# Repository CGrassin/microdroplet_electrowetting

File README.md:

# µDroplet - Microfluidics platform

Microfluidics is an area of research based on the manipulation of small fluid volumes on the order of microliters or nanoliters.

µDroplet is an open-source platform with an 8&times;8 array of electrodes driven by a high voltage to expermiment with various microfluidics techniques and materials.

See article here: https://charleslabs.fr/en/project-Microfluidics+Electrowetting+platform

## Content

This repository contains:
* The PCB (including BOM and gerber files),
* The Arduino firmware
* The Processing control software
* The STL/CAD files for the 3D-printable base and frame

## License

The content of this repository is under MIT license.

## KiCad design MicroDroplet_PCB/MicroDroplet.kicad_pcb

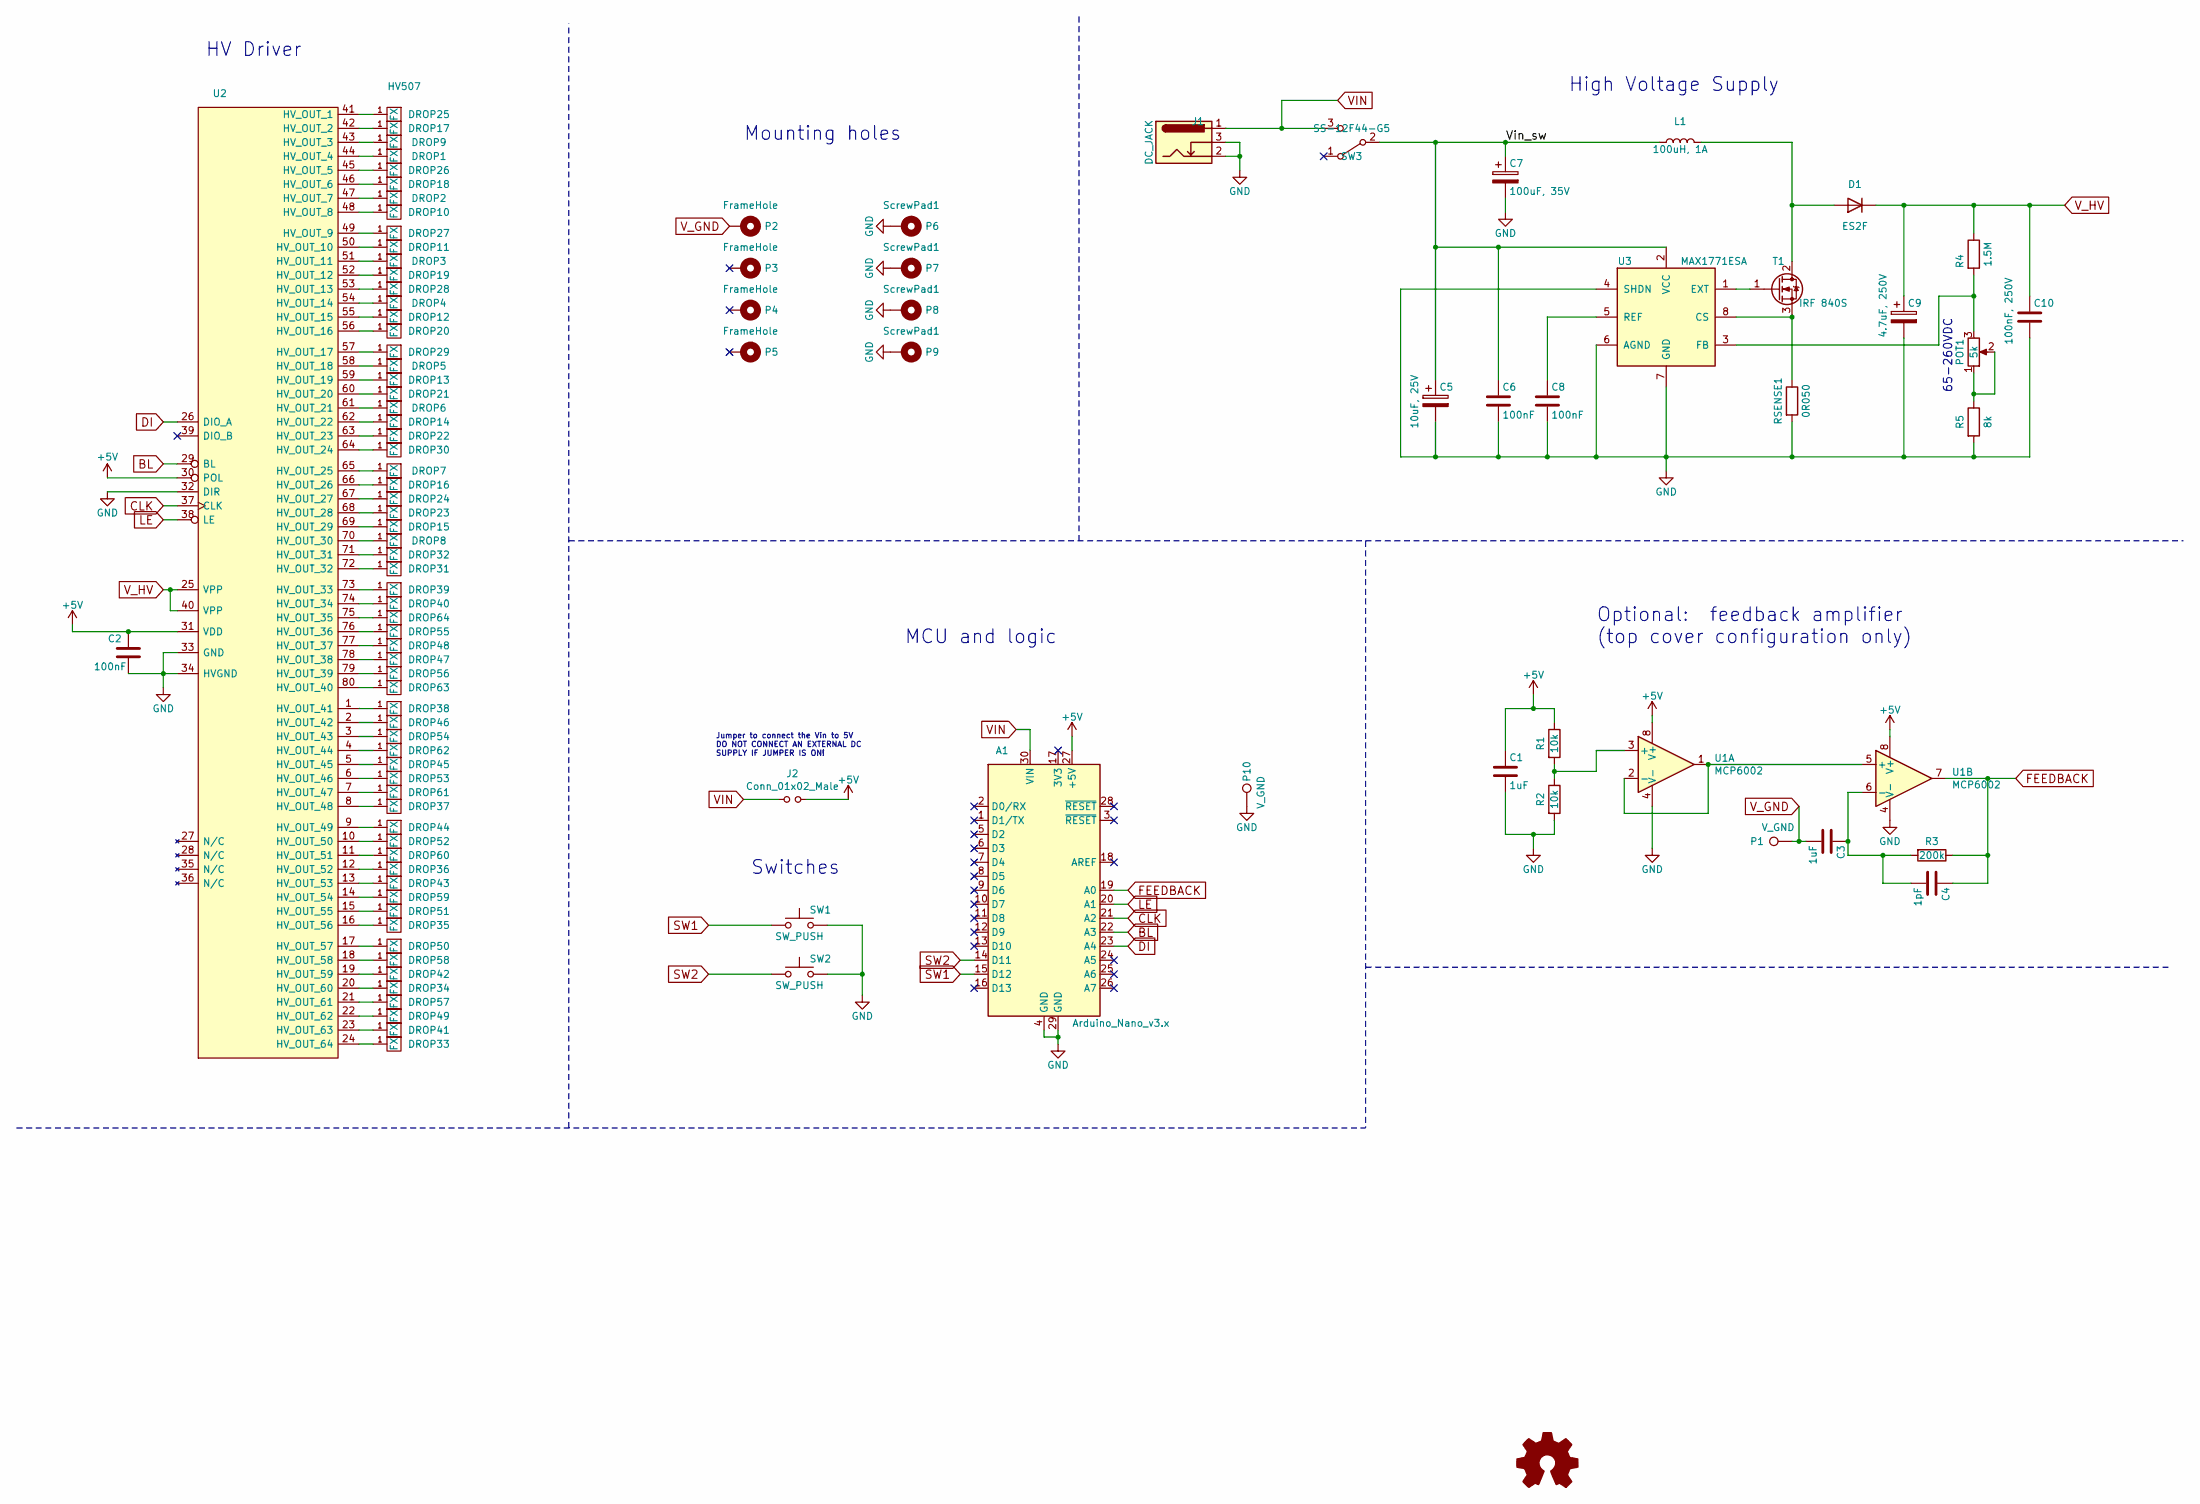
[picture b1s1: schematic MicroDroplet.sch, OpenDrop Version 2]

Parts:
A1: Arduino_Nano_v3.x; Arduino_Nano
C1, C3: 1uF; C_0805_2012Metric_Pad1.15x1.40mm_HandSolder; LCSC C28323
C2, C6, C8: 100nF; C_0805_2012Metric_Pad1.15x1.40mm_HandSolder; LCSC C476766
C4: 1pF; C_0805_2012Metric_Pad1.15x1.40mm_HandSolder; LCSC C1786
C5: 10uF, 25V; CP_Elec_5x5.4; LCSC C72487
C7: 100uF, 35V; CP_Elec_6.3x7.7; LCSC C99837
C9: 4.7uF, 250V; CP_Elec_10x10.5; LCSC C88703
C10: 100nF, 250V; C_1206_3216Metric_Pad1.42x1.75mm_HandSolder; LCSC C338139
D1: ES2F; D_SMB_Handsoldering; LCSC C145321
DROP1, DROP2, DROP3, DROP4, DROP5, DROP6, DROP7, DROP8, DROP9, DROP10, DROP11, DROP12, DROP13, DROP14, DROP15, DROP16, DROP17, DROP18, DROP19, DROP20, DROP21, DROP22, DROP23, DROP24, DROP25, DROP26, DROP27, DROP28, DROP29, DROP30, DROP31, DROP32, DROP33, DROP34, DROP35, DROP36, DROP37, DROP38, DROP39, DROP40, DROP41, DROP42, DROP43, DROP44, DROP45, DROP46, DROP47, DROP48, DROP49, DROP50, DROP51, DROP52, DROP53, DROP54, DROP55, DROP56, DROP57, DROP58, DROP59, DROP60, DROP61, DROP62, DROP63, DROP64: FX; DROP_2_75_4MIL_4_5
J1: DC_JACK; BarrelJack_Horizontal; LCSC C16214
J2: Conn_01x02_Male; PinHeader_1x02_P2.54mm_Vertical; LCSC C124375
L1: 100uH, 1A; L_Bourns_SRR1210A; LCSC C237992
LOGO1: Logo_Open_Hardware_Small; Charleslabs_Logo_10mm
P1, P10: V_GND; TestPoint_THTPad_D2.0mm_Drill1.0mm
P2: FrameHole; MountingHole_3.2mm_M3_Pad
P3, P4, P5: FrameHole; MountingHole_3.2mm_M3
P6, P7, P8, P9: ScrewPad1; MountingHole_3.2mm_M3_Pad
POT1: 5k; BOURNS-3362P_pot; LCSC C116296
R1, R2: 10k; R_0805_2012Metric_Pad1.15x1.40mm_HandSolder; LCSC C38522
R3: 200k; R_0805_2012Metric_Pad1.15x1.40mm_HandSolder; LCSC C104082
R4: 1.5M; R_1206_3216Metric_Pad1.42x1.75mm_HandSolder; LCSC C294796
R5: 8k; R_0805_2012Metric_Pad1.15x1.40mm_HandSolder; LCSC C465485
RSENSE1: 0R050; R_2512_6332Metric_Pad1.52x3.35mm_HandSolder; LCSC C160588
SW1, SW2: SW_PUSH; SW_PUSH_6mm; LCSC C393938
SW3: SS-12F44-G5; SPDT_12.1_5.6; LCSC C136718
T1: IRF 840S; TO-263-2; LCSC C134927
U1: MCP6002; SOIC-8_3.9x4.9mm_P1.27mm; LCSC C7377
U2: HV507; PQFP-80_14x20mm_P0.8mm
U3: MAX1771ESA; SOIC-8_3.9x4.9mm_P1.27mm

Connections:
+5V: A1.27 (+5V), C1.1, C2.1, J2.2, R1.1, U1.8 (V+), U2.30 (POL), U2.31 (VDD)
/Vin_sw: C5.1, C6.1, C7.1, L1.1, SW3.2 (B), U3.2 (VCC)
BL: A1.22 (A3), U2.29 (BL)
CLK: A1.21 (A2), U2.37 (CLK)
DI: A1.23 (A4), U2.26 (DIO_A)
FEEDBACK: A1.19 (A0), C4.1, R3.1, U1.7
GND: A1.4 (GND), A1.29 (GND), C1.2, C2.2, C5.2, C6.2, C7.2, C8.2, C9.2, C10.2, J1.2, J1.3, P6.1, P7.1, P8.1, P9.1, P10.1, R2.2, R5.2, RSENSE1.2, SW1.2, SW2.2, U1.4 (V-), U2.32 (DIR), U2.33 (GND), U2.34 (HVGND), U3.4 (SHDN), U3.6 (AGND), U3.7 (GND)
LE: A1.20 (A1), U2.38 (LE)
unnamed: C3.1, C4.2, R3.2, U1.6 (-)
unnamed: C8.1, U3.5 (REF)
unnamed: D1.2 (A), L1.2, T1.2 (D)
unnamed: DROP1.1, U2.44 (HV_OUT_4)
unnamed: DROP2.1, U2.47 (HV_OUT_7)
unnamed: DROP3.1, U2.51 (HV_OUT_11)
unnamed: DROP4.1, U2.54 (HV_OUT_14)
unnamed: DROP5.1, U2.58 (HV_OUT_18)
unnamed: DROP6.1, U2.61 (HV_OUT_21)
unnamed: DROP7.1, U2.65 (HV_OUT_25)
unnamed: DROP8.1, U2.70 (HV_OUT_30)
unnamed: DROP9.1, U2.43 (HV_OUT_3)
unnamed: DROP10.1, U2.48 (HV_OUT_8)
unnamed: DROP11.1, U2.50 (HV_OUT_10)
unnamed: DROP12.1, U2.55 (HV_OUT_15)
unnamed: DROP13.1, U2.59 (HV_OUT_19)
unnamed: DROP14.1, U2.62 (HV_OUT_22)
unnamed: DROP15.1, U2.69 (HV_OUT_29)
unnamed: DROP16.1, U2.66 (HV_OUT_26)
unnamed: DROP17.1, U2.42 (HV_OUT_2)
unnamed: DROP18.1, U2.46 (HV_OUT_6)
unnamed: DROP19.1, U2.52 (HV_OUT_12)
unnamed: DROP20.1, U2.56 (HV_OUT_16)
unnamed: DROP21.1, U2.60 (HV_OUT_20)
unnamed: DROP22.1, U2.63 (HV_OUT_23)
unnamed: DROP23.1, U2.68 (HV_OUT_28)
unnamed: DROP24.1, U2.67 (HV_OUT_27)
unnamed: DROP25.1, U2.41 (HV_OUT_1)
unnamed: DROP26.1, U2.45 (HV_OUT_5)
unnamed: DROP27.1, U2.49 (HV_OUT_9)
unnamed: DROP28.1, U2.53 (HV_OUT_13)
unnamed: DROP29.1, U2.57 (HV_OUT_17)
unnamed: DROP30.1, U2.64 (HV_OUT_24)
unnamed: DROP31.1, U2.72 (HV_OUT_32)
unnamed: DROP32.1, U2.71 (HV_OUT_31)
unnamed: DROP33.1, U2.24 (HV_OUT_64)
unnamed: DROP34.1, U2.20 (HV_OUT_60)
unnamed: DROP35.1, U2.16 (HV_OUT_56)
unnamed: DROP36.1, U2.12 (HV_OUT_52)
unnamed: DROP37.1, U2.8 (HV_OUT_48)
unnamed: DROP38.1, U2.1 (HV_OUT_41)
unnamed: DROP39.1, U2.73 (HV_OUT_33)
unnamed: DROP40.1, U2.74 (HV_OUT_34)
unnamed: DROP41.1, U2.23 (HV_OUT_63)
unnamed: DROP42.1, U2.19 (HV_OUT_59)
unnamed: DROP43.1, U2.13 (HV_OUT_53)
unnamed: DROP44.1, U2.9 (HV_OUT_49)
unnamed: DROP45.1, U2.5 (HV_OUT_45)
unnamed: DROP46.1, U2.2 (HV_OUT_42)
unnamed: DROP47.1, U2.78 (HV_OUT_38)
unnamed: DROP48.1, U2.77 (HV_OUT_37)
unnamed: DROP49.1, U2.22 (HV_OUT_62)
unnamed: DROP50.1, U2.17 (HV_OUT_57)
unnamed: DROP51.1, U2.15 (HV_OUT_55)
unnamed: DROP52.1, U2.10 (HV_OUT_50)
unnamed: DROP53.1, U2.6 (HV_OUT_46)
unnamed: DROP54.1, U2.3 (HV_OUT_43)
unnamed: DROP55.1, U2.76 (HV_OUT_36)
unnamed: DROP56.1, U2.79 (HV_OUT_39)
unnamed: DROP57.1, U2.21 (HV_OUT_61)
unnamed: DROP58.1, U2.18 (HV_OUT_58)
unnamed: DROP59.1, U2.14 (HV_OUT_54)
unnamed: DROP60.1, U2.11 (HV_OUT_51)
unnamed: DROP61.1, U2.7 (HV_OUT_47)
unnamed: DROP62.1, U2.4 (HV_OUT_44)
unnamed: DROP63.1, U2.80 (HV_OUT_40)
unnamed: DROP64.1, U2.75 (HV_OUT_35)
unnamed: POT1.1, POT1.2, R5.1
unnamed: POT1.3, R4.2, U3.3 (FB)
unnamed: R1.2, R2.1, U1.3 (+)
unnamed: RSENSE1.1, T1.3 (S), U3.8 (CS)
unnamed: T1.1 (G), U3.1 (EXT)
unnamed: U1.1, U1.2 (-), U1.5 (+)
SW1: A1.15 (D12), SW1.1
SW2: A1.14 (D11), SW2.1
VIN: A1.30 (VIN), J1.1, J2.1, SW3.3 (C)
V_GND: C3.2, P1.1, P2.1
V_HV: C9.1, C10.1, D1.1 (K), R4.1, U2.25 (VPP), U2.40 (VPP)

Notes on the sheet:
65-260VDC
High Voltage Supply
HV Driver
Switches
Jumper to connect the Vin to 5V DO NOT CONNECT AN EXTERNAL DC SUPPLY IF JUMPER IS ON!
Optional: feedback amplifier (top cover configuration only)
Mounting holes
MCU and logic

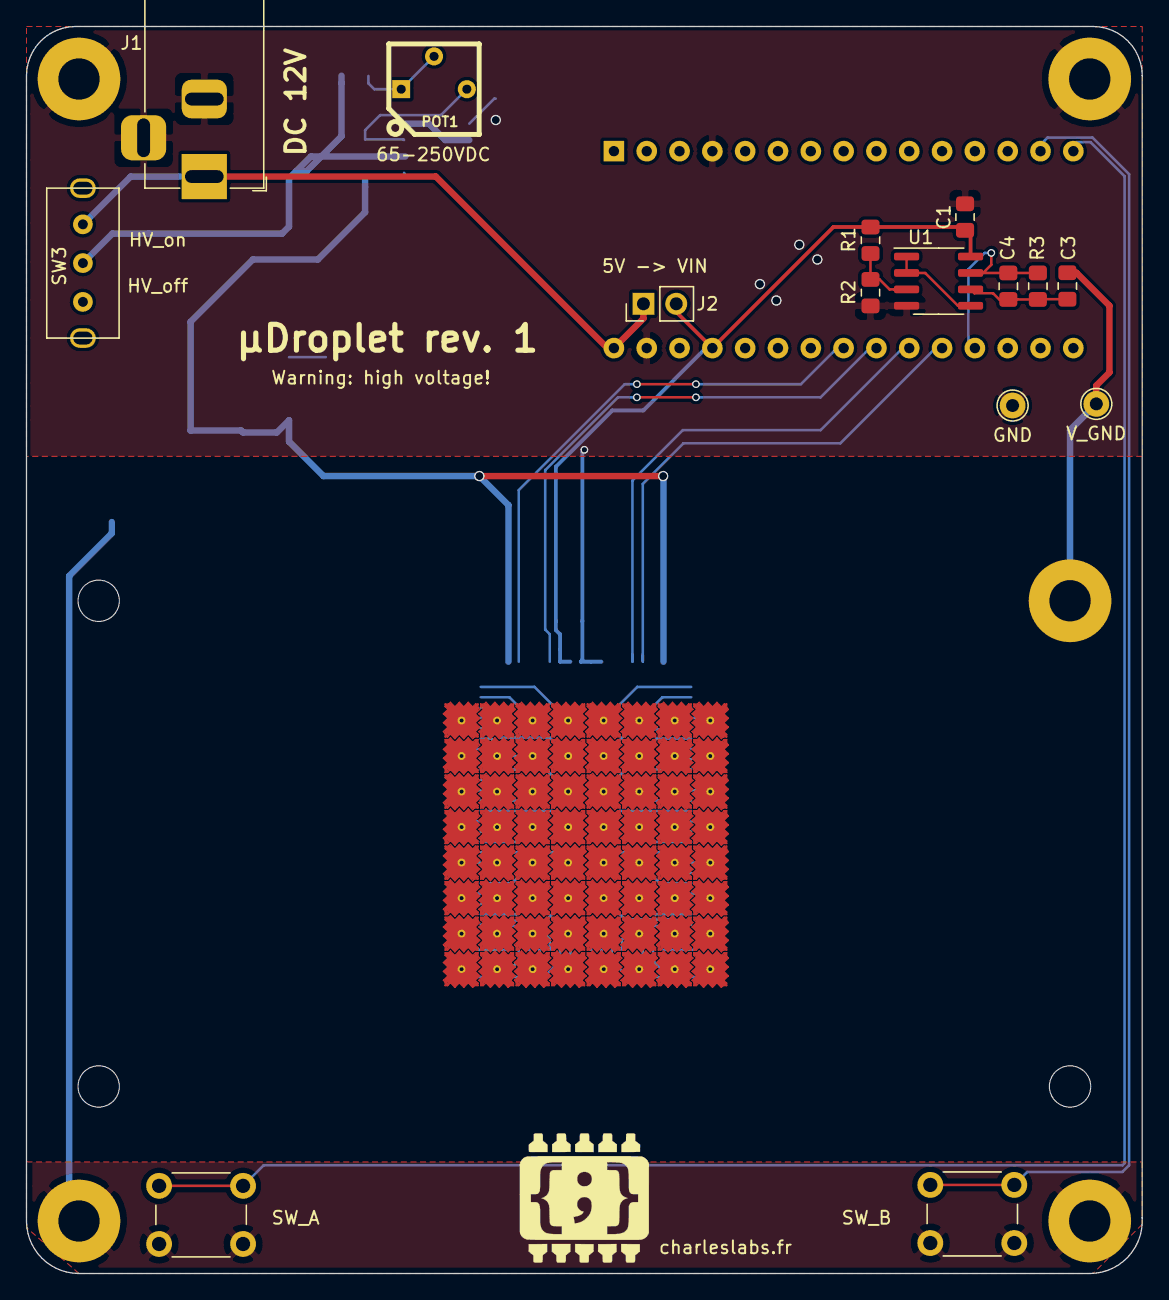
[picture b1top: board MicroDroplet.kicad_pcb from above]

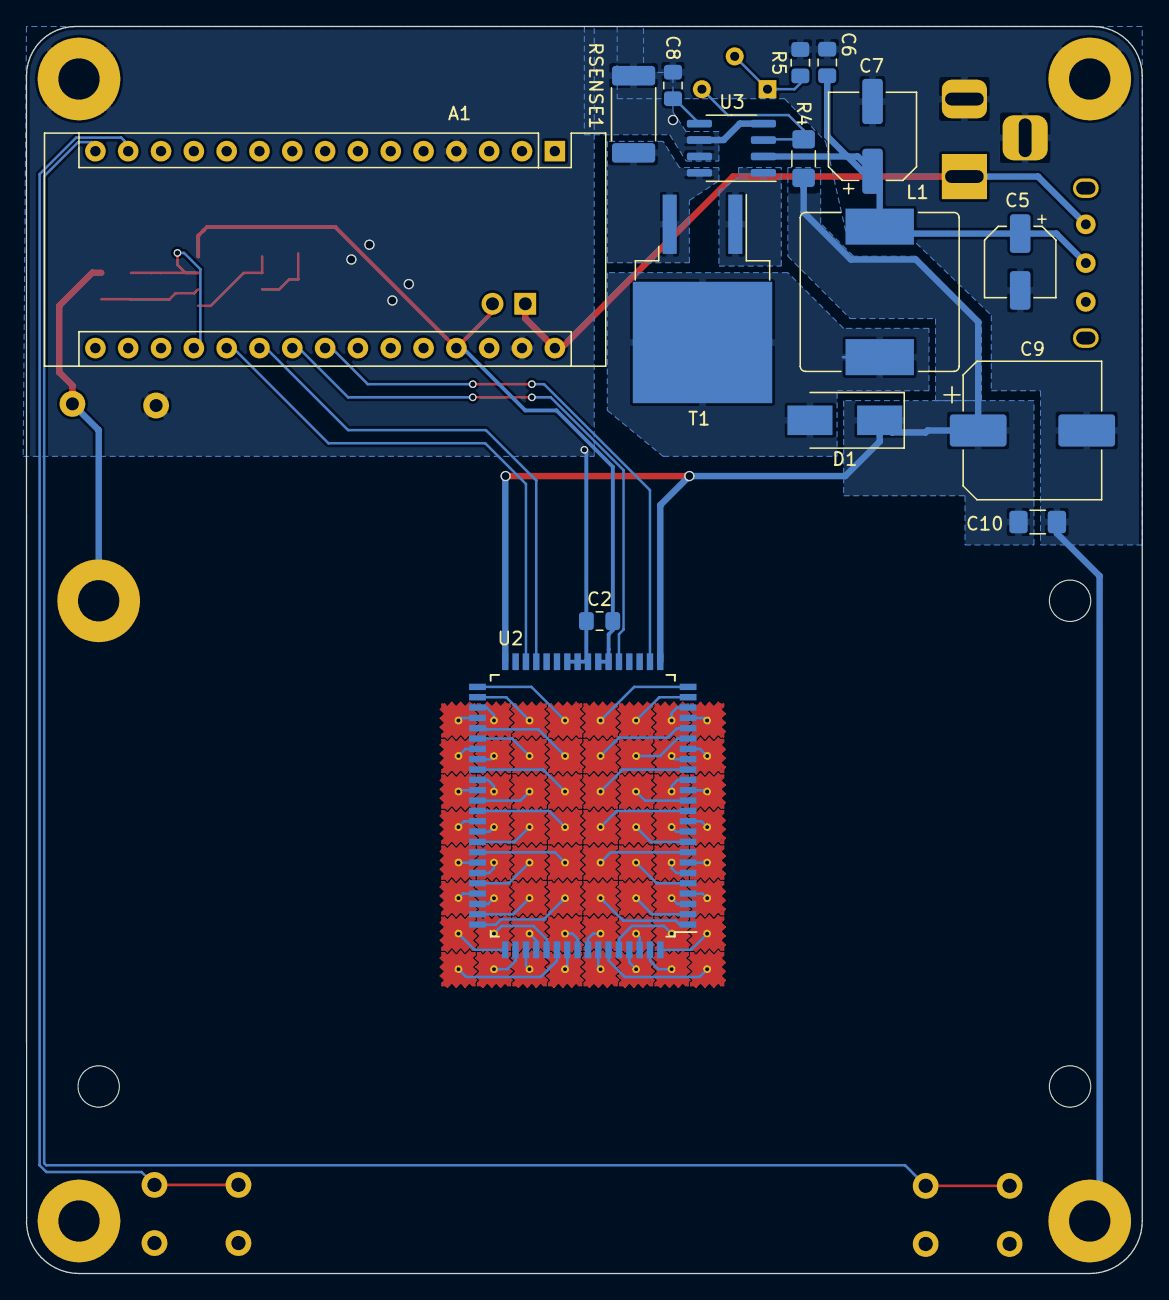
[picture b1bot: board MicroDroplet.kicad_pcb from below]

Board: 2 copper layers, 86.4 x 96.5 mm, 104 parts (16 on the bottom side), 86 nets.

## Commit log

2021-01-20 Improved serial read speed
2021-01-21 Improved serial performance, added GUI controls
